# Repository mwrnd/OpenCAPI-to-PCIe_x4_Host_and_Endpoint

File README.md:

**Work-In-Progress**: Design being tested.

# OpenCAPI to PCIe x4 Host and Endpoint

Designed to test simultaneous PCIe Host and Endpoint operation with the Innova-2.

There are two [PCIE4](https://docs.xilinx.com/r/en-US/pg213-pcie4-ultrascale-plus/Introduction) blocks in the column of the Innova-2's OpenCAPI Quads.

The GTY Transceivers connected to the OpenCAPI Connector are in a column that does not contain the Configuration Block so it is impossible for the FPGA to be programmed within the [100ms PCIe power-up time limit](https://pcisig.com/specifications/ecr_ecn_process?speclib=100+ms). Motherboard boot must be delayed to allow the FPGA to configure itself before PCIe devices are enumerated. This can be accomplished by toggling the POWER button, then pressing and holding the RESET button for a second before releasing it. Or, [connect a capacitor across the reset pins of an ATX motherboard's Front Panel Header](https://github.com/mwrnd/ATX_Boot_Delay).

[OpenCAPI](https://files.openpower.foundation/s/xSQPe6ypoakKQdq/download/25Gbps-spec-20171108.pdf)-compatible SlimSAS 8x uses a **Host** version of the OpenCAPI **Carrier** pinout from the [ADM-PCIE-9V5 User Manual (Pg15-19of38)](https://www.alpha-data.com/xml/user_manuals/adm-pcie-9v5%20user%20manual_v1_4.pdf).

## Testing

```
TODO
```

### OpenCAPI I2C

The [innova2_xdma_opencapi](https://github.com/mwrnd/innova2_xdma_opencapi) project includes the ability to test I2C.

## PCB Layout

All differential pairs are length-matched to within 1mm intra-pair (N-to-P) and each group of differential pairs (e.g., TX0-to-TX3) is similarly matched to within 1mm.

## Schematic

## Bill Of Materials

| Designator(s) | Part Number             | Quantity | Value      | Footprint                           | Availability                                                                                               |
| ------------- | ----------------------- | -------- | ---------- | ----------------------------------- | ---------------------------------------------------------------------------------------------------------- |
| U1            | SY75572LMG              |        1 |        N/A | QFN-16-1EP_3x3mm_P0.5mm             | [DigiKey](https://www.digikey.com/en/products/detail/microchip-technology/SY75572LMG-TR/5319585)           |
| U2            | DSC1124BI2-100-0000     |        1 |        N/A | OSC_SMD_IDT_JS6-6_5.0x3.2mm_P1.27mm | [DigiKey](https://www.digikey.com/en/products/detail/microchip-technology/DSC1124BI2-100-0000/5284202)     |
| J1            | U10A474240T             |        1 |        N/A | SlimSAS_8x_RA_U10-A474              | [DigiKey](https://www.digikey.com/en/products/detail/amphenol-cs-commercial-products/U10A474240T/17066204) |
| J2            | PPPC061LFBN-RC          |        1 |        N/A | PinHeader_1x06_P2.54mm_Vertical     | [DigiKey](https://www.digikey.com/en/products/detail/sullins-connector-solutions/PPPC061LFBN-RC/810178)    |
| J4            | 2-2387405-2             |        1 |        N/A | PCIe x4 Straddle Mount w/ Open End  | [DigiKey](https://www.digikey.com/en/products/detail/te-connectivity-amp-connectors/2-2387405-2/15221995)    |
| JP1           | 2PH1-02-UA              |        1 |        N/A | PinHeader_1x02_P2.00mm_Vertical     | [DigiKey](https://www.digikey.com/en/products/detail/adam-tech/2PH1-02-UA/9830305)                         |
| R31 to R36    | RT0402FRE0733RL         |        6 |     33-Ohm | Resistor_SMD_R_0402_1005Metric      | [DigiKey](https://www.digikey.com/en/products/detail/yageo/RT0402FRE0733RL/1071963)                        |
| R51 to R56    | RT0402FRE0749R9L        |        6 |   49.9-Ohm | Resistor_SMD_R_0402_1005Metric      | [DigiKey](https://www.digikey.com/en/products/detail/yageo/RT0402FRE0749R9L/1072042)                       |
| R1            | RT0402FRE07475RL        |        1 |    475-Ohm | Resistor_SMD_R_0402_1005Metric      | [DigiKey](https://www.digikey.com/en/products/detail/yageo/RT0402FRE07475RL/1072032)                       |
| R2, R5        | RT0402FRE0751KL         |        2 |    51k-Ohm | Resistor_SMD_R_0402_1005Metric      | [DigiKey](https://www.digikey.com/en/products/detail/yageo/RT0402FRE0751KL/1072058)                        |
| L1, L2        | BLM15PX601SN1D          |        2 | 600@100MHz | Resistor_SMD_R_0402_1005Metric      | [DigiKey](https://www.digikey.com/en/products/detail/murata-electronics/BLM15PX601SN1D/4421102)            |
| C4            | KGM05AR71C103KH         |        1 |     0.01uF | Capacitor_SMD_C_0402_1005Metric     | [DigiKey](https://www.digikey.com/en/products/detail/kyocera-avx/KGM05AR71C103KH/563224)                   |
| C1, C2, C3    | KGM05AR51A104KH         |        3 |      0.1uF | Capacitor_SMD_C_0402_1005Metric     | [DigiKey](https://www.digikey.com/en/products/detail/kyocera-avx/KGM05AR51A104KH/563239)                   |
| C5            | CL21B105KAFNNNE         |        1 |        1uF | Capacitor_SMD_C_0805_2012Metric     | [DigiKey](https://www.digikey.com/en/products/detail/samsung-electro-mechanics/CL21B105KAFNNNE/3886724)    |
| J7, J8        | 2337019-1               |        2 | U.FL(UMCC) | U.FL_Hirose                         | [DigiKey](https://www.digikey.com/en/products/detail/te-connectivity-amp-connectors/2337019-1/9974052)     |
| Jumper        | SPN02SYBN-RC            |        1 |        N/A | 2mm Shunt                           | [DigiKey](https://www.digikey.com/en/products/detail/sullins-connector-solutions/SPN02SYBN-RC/927356)      |

**Optional**: [TC74Ax-3-3VAT](https://www.digikey.com/en/products/detail/microchip-technology/TC74A0-3-3VAT/442720) I2C Temperature Sensor for testing I2C.

## Assembly Notes

Use needle-nosed pliers to remove the PCIe x4 Connector's mounting post.

Three wire jumpers are needed to connect `3V3==3V3_PCIe`, `nPERST==RST`, and `nPRSNT1==nPRSNT2_x4`.

## PCB Layer Stackup

4-Layer PCB stackup taken from [JLCPCB](https://jlcpcb.com/capabilities/pcb-capabilities).

Differential Impedance parameters were calculated using the [DigiKey Online Calculator](https://www.digikey.com/en/resources/conversion-calculators/conversion-calculator-pcb-trace-impedance).

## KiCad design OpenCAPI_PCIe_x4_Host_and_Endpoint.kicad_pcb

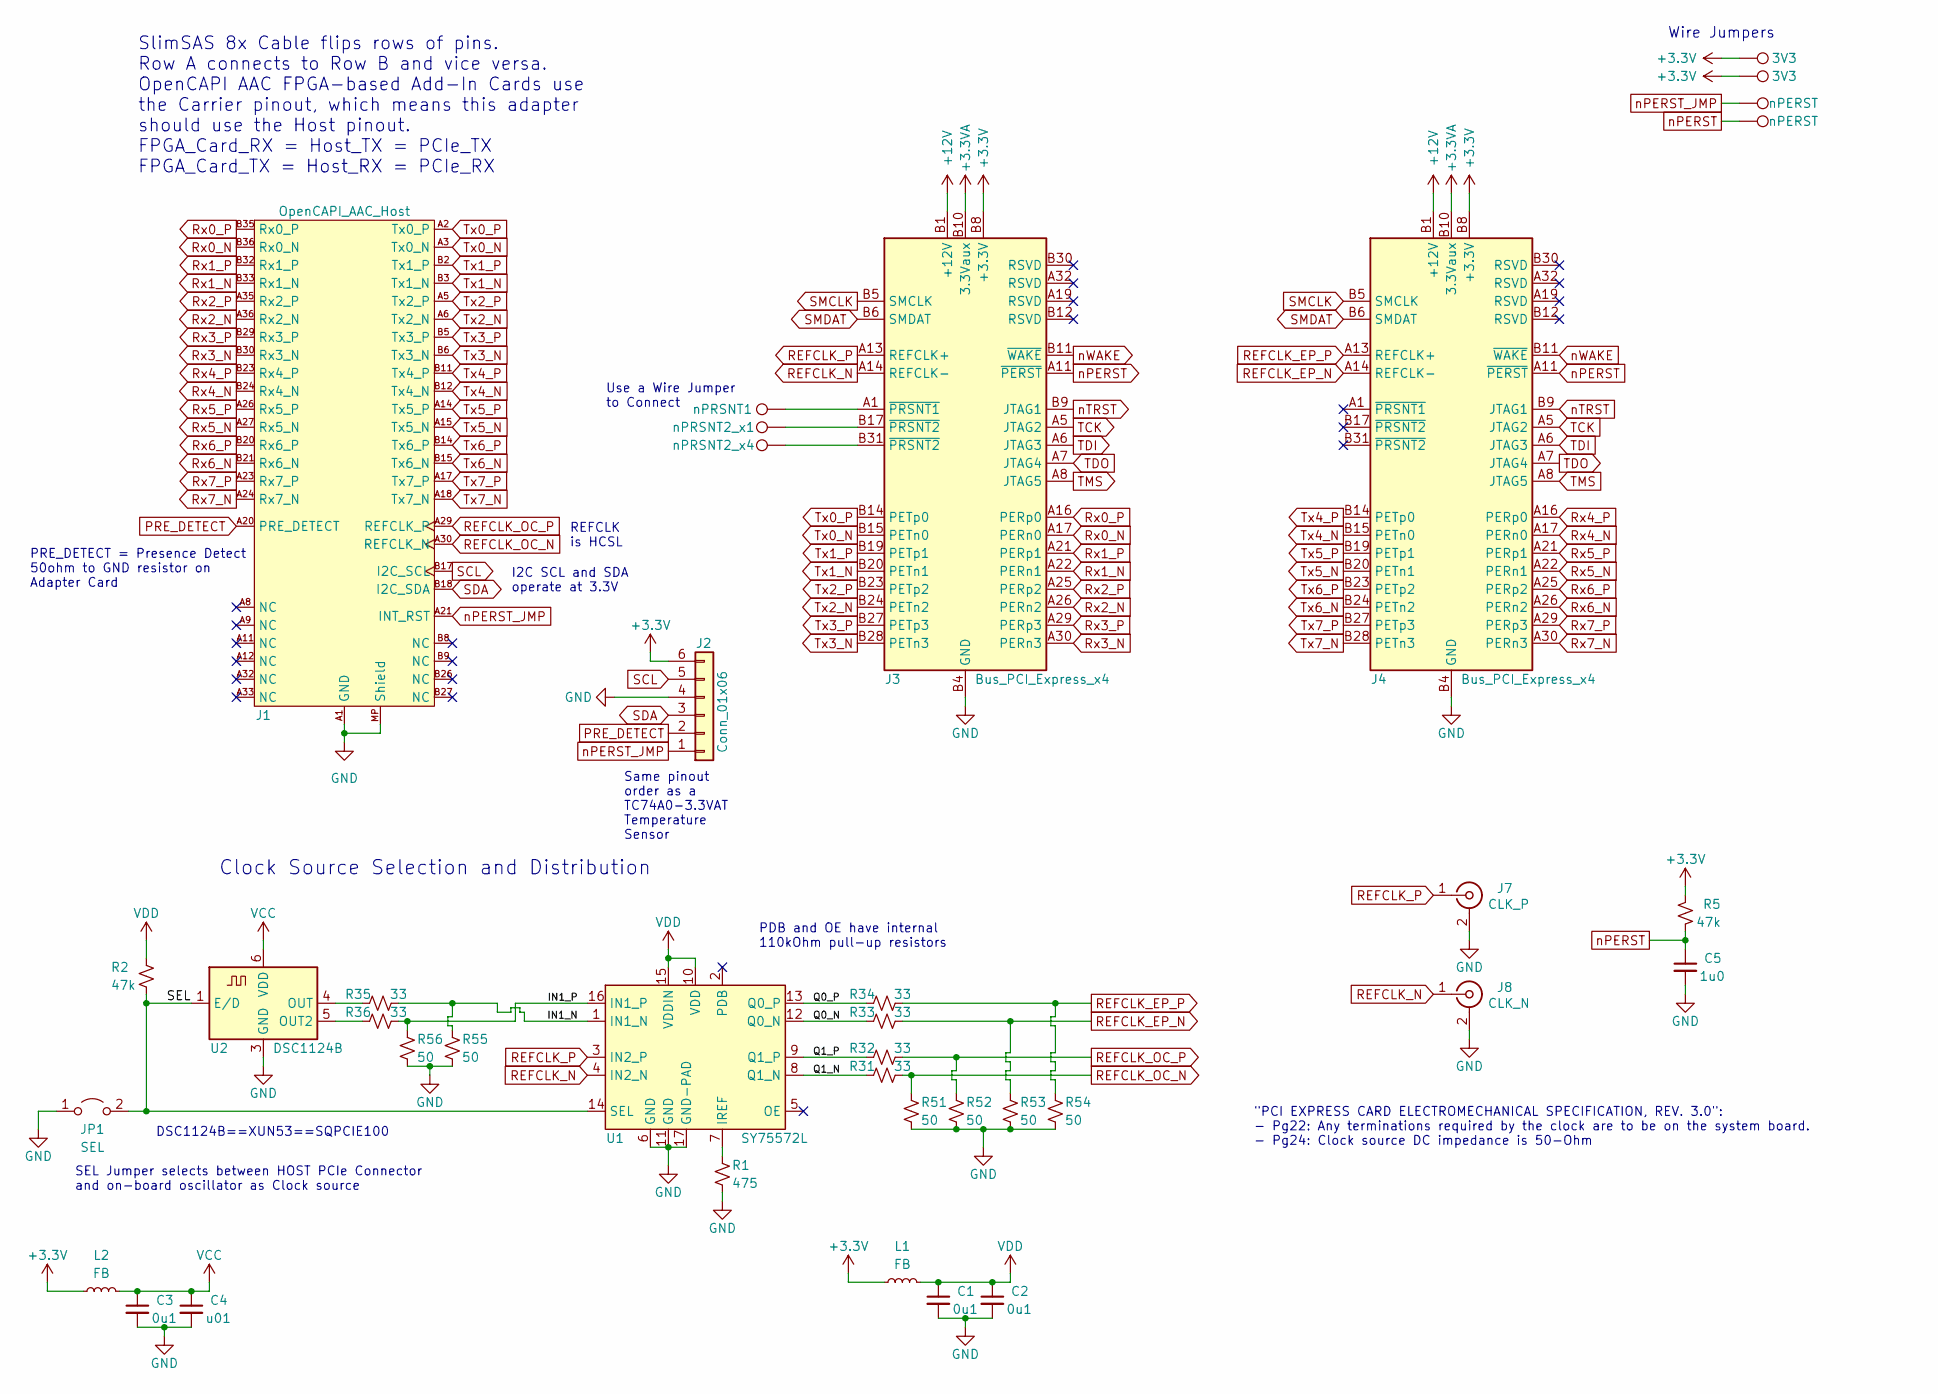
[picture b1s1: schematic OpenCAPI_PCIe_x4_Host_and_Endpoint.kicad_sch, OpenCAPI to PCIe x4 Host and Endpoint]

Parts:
C1, C2, C3: 0u1; C_0402_1005Metric_Pad0.74x0.62mm_HandSolder
C4: u01; C_0402_1005Metric_Pad0.74x0.62mm_HandSolder
C5: 1u0; C_0805_2012Metric_Pad1.18x1.45mm_HandSolder
J1: OpenCAPI_AAC_Host; SlimSAS_8x_RA_U10-A474
J2: Conn_01x06; PinHeader_1x06_P2.54mm_Vertical
J3, J4: Bus_PCI_Express_x4; BUS_PCIexpress_x4
J7: CLK_P; U.FL_Hirose_w_Label
J8: CLK_N; U.FL_Hirose_w_Label
JP1: SEL; PinHeader_1x02_P2.00mm_Vertical
L1, L2: FB; R_0402_1005Metric_Pad0.72x0.64mm_HandSolder
R1: 475; R_0402_1005Metric_Pad0.72x0.64mm_HandSolder
R2, R5: 47k; R_0402_1005Metric_Pad0.72x0.64mm_HandSolder
R31, R32, R33, R34, R35, R36: 33; R_0402_1005Metric_Pad0.72x0.64mm_HandSolder
R51, R52, R53, R54, R55, R56: 50; R_0402_1005Metric_Pad0.72x0.64mm_HandSolder
TP1: nPRSNT1; TestPoint_THTPad_D1.0mm_Drill0.5mm
TP2: nPRSNT2_x1; TestPoint_THTPad_D1.0mm_Drill0.5mm
TP3: nPRSNT2_x4; TestPoint_THTPad_D1.0mm_Drill0.5mm
TP4, TP5: 3V3; TestPoint_THTPad_D1.0mm_Drill0.5mm
TP6, TP7: nPERST; TestPoint_THTPad_D1.0mm_Drill0.5mm
U1: SY75572L; QFN-16-1EP_3x3mm_P0.5mm_EP1.45x1.45mm_ThermalVias
U2: DSC1124B; Oscillator_SMD_IDT_JS6-6_5.0x3.2mm_P1.27mm

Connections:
+3.3V: J2.6, J3.A9 (+3.3V), J3.A10 (+3.3V), J3.B8 (+3.3V), J4.A9 (+3.3V), J4.A10 (+3.3V), J4.B8 (+3.3V), L1.1, L2.1, R5.1, TP4.1, TP5.1
+3.3VA: J3.B10 (3.3Vaux), J4.B10 (3.3Vaux)
+12V: J3.A2 (+12V), J3.A3 (+12V), J3.B1 (+12V), J3.B2 (+12V), J3.B3 (+12V), J4.A2 (+12V), J4.A3 (+12V), J4.B1 (+12V), J4.B2 (+12V), J4.B3 (+12V)
/IN1_N: R35.1, R55.1, U1.1 (IN1_N)
/IN1_P: R36.1, R56.1, U1.16 (IN1_P)
/Q0_N: R33.2, U1.12 (Q0_N)
/Q0_P: R34.2, U1.13 (Q0_P)
/Q1_N: R31.2, U1.8 (Q1_N)
/Q1_P: R32.2, U1.9 (Q1_P)
/SEL: JP1.2 (B), R2.2, U1.14 (SEL), U2.1 (E/D)
GND: C1.2, C2.2, C3.2, C4.2, C5.2, J1.A1 (GND), J1.A4 (GND), J1.A7 (GND), J1.A10 (GND), J1.A13 (GND), J1.A16 (GND), J1.A19 (GND), J1.A22 (GND), J1.A25 (GND), J1.A28 (GND), J1.A31 (GND), J1.A34 (GND), J1.A37 (GND), J1.B1 (GND), J1.B4 (GND), J1.B7 (GND), J1.B10 (GND), J1.B13 (GND), J1.B16 (GND), J1.B19 (GND), J1.B22 (GND), J1.B25 (GND), J1.B28 (GND), J1.B31 (GND), J1.B34 (GND), J1.B37 (GND), J1.MP (Shield), J2.4, J3.A4 (GND), J3.A12 (GND), J3.A15 (GND), J3.A18 (GND), J3.A20 (GND), J3.A23 (GND), J3.A24 (GND), J3.A27 (GND), J3.A28 (GND), J3.A31 (GND), J3.B4 (GND), J3.B7 (GND), J3.B13 (GND), J3.B16 (GND), J3.B18 (GND), J3.B21 (GND), J3.B22 (GND), J3.B25 (GND), J3.B26 (GND), J3.B29 (GND), J3.B32 (GND), J4.A4 (GND), J4.A12 (GND), J4.A15 (GND), J4.A18 (GND), J4.A20 (GND), J4.A23 (GND), J4.A24 (GND), J4.A27 (GND), J4.A28 (GND), J4.A31 (GND), J4.B4 (GND), J4.B7 (GND), J4.B13 (GND), J4.B16 (GND), J4.B18 (GND), J4.B21 (GND), J4.B22 (GND), J4.B25 (GND), J4.B26 (GND), J4.B29 (GND), J4.B32 (GND), J7.2 (Ext), J8.2 (Ext), JP1.1 (A), R1.2, R51.2, R52.2, R53.2, R54.2, R55.2, R56.2, U1.6 (GND), U1.11 (GND), U1.17 (GND-PAD), U2.3 (GND)
unnamed: J3.A1 (~PRSNT1), TP1.1
unnamed: J3.B17 (~PRSNT2), TP2.1
unnamed: J3.B31 (~PRSNT2), TP3.1
unnamed: R1.1, U1.7 (IREF)
unnamed: R36.2, U2.5 (OUT2)
unnamed: R35.2, U2.4 (OUT)
PRE_DETECT: J1.A20 (PRE_DETECT), J2.2
REFCLK_EP_N: J4.A14 (REFCLK-), R33.1, R53.1
REFCLK_EP_P: J4.A13 (REFCLK+), R34.1, R54.1
REFCLK_N: J3.A14 (REFCLK-), J8.1 (In), U1.4 (IN2_N)
REFCLK_OC_N: J1.A30 (REFCLK_N), R31.1, R51.1
REFCLK_OC_P: J1.A29 (REFCLK_P), R32.1, R52.1
REFCLK_P: J3.A13 (REFCLK+), J7.1 (In), U1.3 (IN2_P)
Rx0_N: J1.B36 (Rx0_N), J3.A17 (PERn0)
Rx0_P: J1.B35 (Rx0_P), J3.A16 (PERp0)
Rx1_N: J1.B33 (Rx1_N), J3.A22 (PERn1)
Rx1_P: J1.B32 (Rx1_P), J3.A21 (PERp1)
Rx2_N: J1.A36 (Rx2_N), J3.A26 (PERn2)
Rx2_P: J1.A35 (Rx2_P), J3.A25 (PERp2)
Rx3_N: J1.B30 (Rx3_N), J3.A30 (PERn3)
Rx3_P: J1.B29 (Rx3_P), J3.A29 (PERp3)
Rx4_N: J1.B24 (Rx4_N), J4.A17 (PERn0)
Rx4_P: J1.B23 (Rx4_P), J4.A16 (PERp0)
Rx5_N: J1.A27 (Rx5_N), J4.A22 (PERn1)
Rx5_P: J1.A26 (Rx5_P), J4.A21 (PERp1)
Rx6_N: J1.B21 (Rx6_N), J4.A26 (PERn2)
Rx6_P: J1.B20 (Rx6_P), J4.A25 (PERp2)
Rx7_N: J1.A24 (Rx7_N), J4.A30 (PERn3)
Rx7_P: J1.A23 (Rx7_P), J4.A29 (PERp3)
SCL: J1.B17 (I2C_SCL), J2.5
SDA: J1.B18 (I2C_SDA), J2.3
SMCLK: J3.B5 (SMCLK), J4.B5 (SMCLK)
SMDAT: J3.B6 (SMDAT), J4.B6 (SMDAT)
TCK: J3.A5 (JTAG2), J4.A5 (JTAG2)
TDI: J3.A6 (JTAG3), J4.A6 (JTAG3)
TDO: J3.A7 (JTAG4), J4.A7 (JTAG4)
TMS: J3.A8 (JTAG5), J4.A8 (JTAG5)
Tx0_N: J1.A3 (Tx0_N), J3.B15 (PETn0)
Tx0_P: J1.A2 (Tx0_P), J3.B14 (PETp0)
Tx1_N: J1.B3 (Tx1_N), J3.B20 (PETn1)
Tx1_P: J1.B2 (Tx1_P), J3.B19 (PETp1)
Tx2_N: J1.A6 (Tx2_N), J3.B24 (PETn2)
Tx2_P: J1.A5 (Tx2_P), J3.B23 (PETp2)
Tx3_N: J1.B6 (Tx3_N), J3.B28 (PETn3)
Tx3_P: J1.B5 (Tx3_P), J3.B27 (PETp3)
Tx4_N: J1.B12 (Tx4_N), J4.B15 (PETn0)
Tx4_P: J1.B11 (Tx4_P), J4.B14 (PETp0)
Tx5_N: J1.A15 (Tx5_N), J4.B20 (PETn1)
Tx5_P: J1.A14 (Tx5_P), J4.B19 (PETp1)
Tx6_N: J1.B15 (Tx6_N), J4.B24 (PETn2)
Tx6_P: J1.B14 (Tx6_P), J4.B23 (PETp2)
Tx7_N: J1.A18 (Tx7_N), J4.B28 (PETn3)
Tx7_P: J1.A17 (Tx7_P), J4.B27 (PETp3)
VCC: C3.1, C4.1, L2.2, U2.6 (VDD)
VDD: C1.1, C2.1, L1.2, R2.1, U1.10 (VDD), U1.15 (VDDIN)
nPERST: C5.1, J3.A11 (~PERST), J4.A11 (~PERST), R5.2, TP7.1
nPERST_JMP: J1.A21 (INT_RST), J2.1, TP6.1
nTRST: J3.B9 (JTAG1), J4.B9 (JTAG1)
nWAKE: J3.B11 (~WAKE), J4.B11 (~WAKE)

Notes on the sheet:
PDB and OE have internal 110kOhm pull-up resistors
DSC1124B==XUN53==SQPCIE100
Clock Source Selection and Distribution
I2C SCL and SDA operate at 3.3V
Same pinout order as a TC74A0-3.3VAT Temperature Sensor
"PCI EXPRESS CARD ELECTROMECHANICAL SPECIFICATION, REV. 3.0": - Pg22: Any terminations required by the clock are to be on the system board. - Pg24: Clock source DC impedance is 50-Ohm
SEL Jumper selects between HOST PCIe Connector and on-board oscillator as Clock source
REFCLK is HCSL
SlimSAS 8x Cable flips rows of pins. Row A connects to Row B and vice versa. OpenCAPI AAC FPGA-based Add-In Cards use the Carrier pinout, which means this adapter should use the Host pinout. FPGA_Card_RX = Host_TX = PCIe_TX FPGA_Card_TX = Host_RX = PCIe_RX
Wire Jumpers
Use a Wire Jumper to Connect
PRE_DETECT = Presence Detect 50ohm to GND resistor on Adapter Card

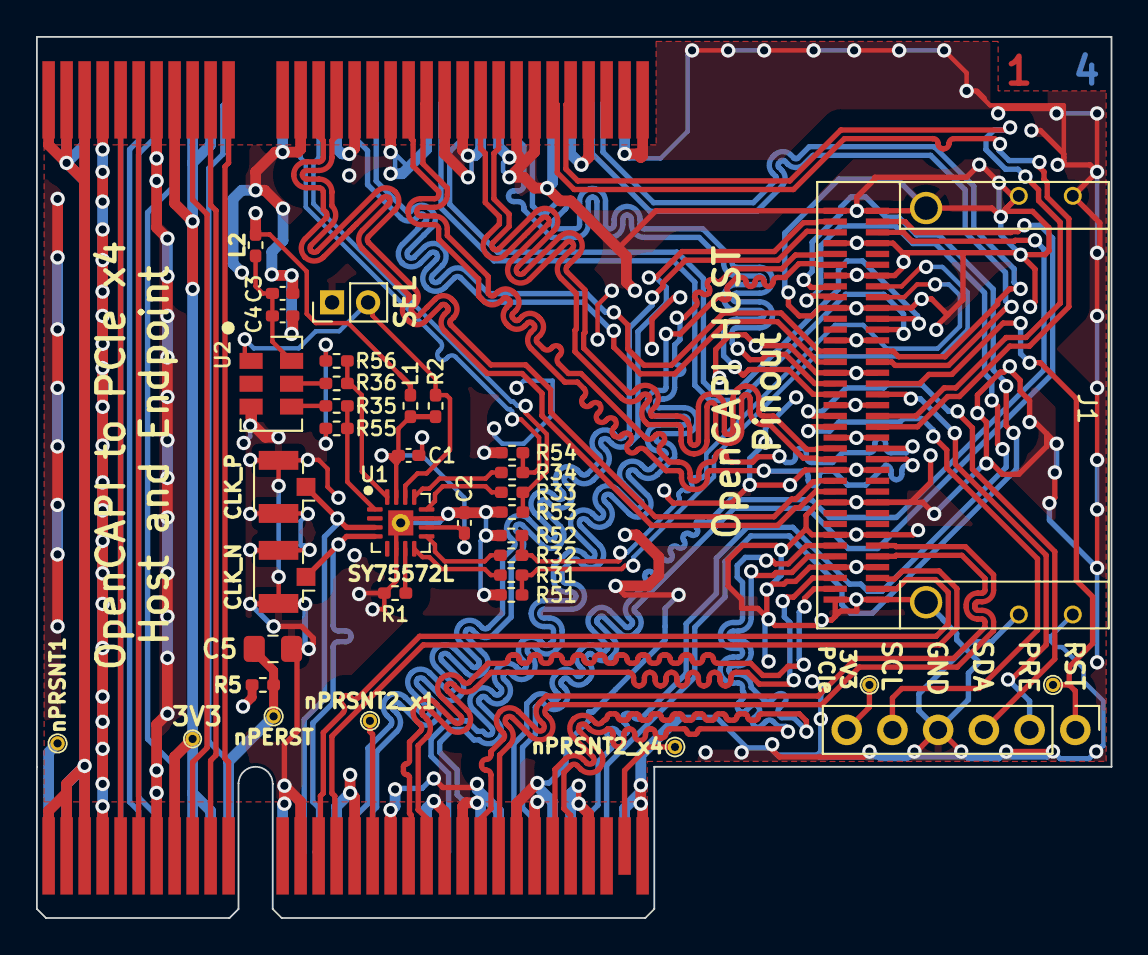
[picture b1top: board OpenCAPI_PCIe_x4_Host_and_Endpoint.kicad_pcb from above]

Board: 4 copper layers, 59.7 x 49.0 mm, 38 parts (0 on the bottom side), 70 nets.

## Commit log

2023-12-16 Work-In-Progress
2023-12-19 First Revision Complete
2024-01-31 Bill Of Materials
